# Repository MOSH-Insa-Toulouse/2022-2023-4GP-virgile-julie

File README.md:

# 2022-2023-4GP-virgile-julie
Projet 4GP du capteur au banc de test en open source hardware
---
## Sommaire
  - [1) Livrables](#1-livrables)
  - [2) Description](#2-description)
  - [3) Shield PCB](#3-shield-pcb)
  - [4) Arduino](#4-arduino)
  - [5) Application Android APK](#5-application-android-apk)
  - [6) Banc de test et mesures](#6-banc-de-test-et-mesures)
  - [7) Datasheet](#7-datasheet)
  - [8) Limites et perspectives](#8-Limites-et-perspectives)
---
## 1) Livrables

Lors de notre projecteur, nous avons décidé de réaliser l'ensemble des options (headers) sur la schématique du shield: 
- capteur
- module bluetooth
- flex sensor
- écran OLED
- potentiomètre digital
 
 Pour se faire, nous avons du réaliser un cahier des charges adaptés:
 
-  Réalisation d'un Shield PCB sur KiCad
-  Réalisation d'un code Arduino permettant la mesure du capteur, ainsi que le réglage du potentiomètre, l'affichage sur un écran OLED, l'envoie des données par module Bluetooth
- Réalisation d'une Application android APK réalisée avec MIT APP INVENTOR
- Réalisation d'une Datasheet du capteur
---
## 2) Description

Dans ce projet, nous allons concevoir un capteur résistif fonctionnant sur la base d'un phénomène physique observé qui est l'effet tunnel. En faisant varier la distance séparant les particules du réseau( par des déformations en compression et en tension), on modifie la conductivité du graphite.

Pour appliquer ce phènomène, la jauge de contrainte sera peu couteuse. Elle se présente sous la forme d’un U en papier, sur lequel on vient déposer du graphite à l’aide d’un crayon à papier ceci est très simple à réaliser et sa fabrication ne génère pas d’impact négatif sur l’environnement. A noter aussi que la réponse du capteur va dépendre du type de mine utilisée. 

Nous avons débuté notre projet par la fabrication de notre shield pour notre chaine de mesures. Ce dernier a été conçu a l'aide du logiciel KICAD  sur la base du amplificateur transimpédance simulation électrique du circuit associé au shield sur le logiciel LTSpice.

Pour exploiter le signal de sortie du capteur par un convertisseur analogique-numérique d’une carte Arduino, la sortie du capteur est reliée à un circuit amplificateur transimpédance. Ce circuit dispose de trois étages de filtrage : 
- Un filtre passe-bas R1C1 qui permet de filtrer les bruits en courants sur le signal d’entrée
- Un filtre passe bas R3C4 couplé à un amplificateur opérationnel LTC1050 permettant de filtrer la composante du bruit à 50 Hz provenant du réseau électrique
- Un filtre de sortie R5C2 qui coupe les bruits due à l’échantillonnage de l’ADC
On retrouve la valeur de résistance du capteur grâce à la formule suivante : 
R=(1+R3/R2)*R1*Vcc/Vadc-R1-R5

Par la suite, nous avons ensuite imprimé notre circuit PCB après validation de celle-ci, qui aura demandé de multiples essais. 
Puis, nous avons réalisé le montage des composants sur la carte vierge avec le matériel ci-dessous.

Matériel nécessaire
* 1 carte Arduino Uno
* 2 Résistance de 100kΩ
* 1 Résistance de 1kΩ
* 1 Potentiomètre digital MCP-41050
* 2 Condensateurs 100nF
* 1 Condensateurs 1µF
* 1 AOP LTC1050
* 1 Écran OLED01
* 1 Module Bluetooth HC-05

Puis, nous avons codé avec l'usage d'une carte Arduino le code permettant la lecture des mesures du capteur ainsi que l'ajout sur le code des fonctions associés aux différentes options ajoutés soit l'écran OLED, le module Bluetooth et le potentiomètre digital.  
Ensuite, nous avons développé une application Android qui a pour but de recevoir des données via Bluetooth grâce le site MIT App Inventor.  
Et enfin, nous avons réalisé notre propre banc de test : nous avons effectué un test de rayon de courbure et un test de répétabilité avec deux types de crayons (2B, HB2).  

---
## 3) Shield PCB

### Réalisation de la Schématique de Shield
Cette partie se consacre à la réalisation et la fabrication du support éléctronique, soit le PCB de notre projet. Il a été réalisé sur le logiciel Kicad en se basant sur le template d'un arduino uno.

Pour se faire, nous avons conçu l'ensemble des symboles et empreintes associés aux options choisis précédements. Avec les empreintes, nous les avons connecté avec le reste du circuit existant afin d'obtenir notre shield.

### Réalisation de la Schématique du PCB
En se basant sur notre Shield, nous avons réalisé le routage de notre circuit en prenant soin de limiter les distances entre les composantes et leur pins associés. Cette étape fut très laboriseuse car le fait d'avoir une seule couche pour le PCB, nous obligeait de trouver des stratagèmes d'optimisation de place et de placement. Lorsque cette étape était fini, nous pouvons passer à la pose du plan de masse de notre circuit.

Comme nous pouvons le voir, le résultant possède néanmoins un fil supplémentaire, un fil rouge, qui sera ajouté lors de la fabrication du shield pour respecter le plan de masse. 

### Fabrication du PCB
Le PCB a été fabriqué à partir d'une plaquette d’époxy recouverte d’une fine couche de cuivre. 

Etapes de fabrication:

* Réaliser une insolation aux UVs de notre plaquette avec le calque de notre circuit (10 minutes)
* Retirer la partie de résine non isolée avec un révélateur
* Plonger notre plaquette dans un bain de percholorure de fer

### Assemblage des composantes
Lorsque le PCB a été fabriqué, il nous reste l'étape d'assemblage du shield. Pour se faire, il nous faut donc percer le PCB et souder les composants.
Pour ce qui est du perçage, dans les consignes, il était dit de prévoir deux tailles de trous sur le Kicad, soit un de diamètre 0,8mm pour les composants et headers et un de diamètre 1mm pour les broches de connexion de la carte Arduino Uno.

## 4) Arduino

Nous avons développé un code Arduino qui permet de récupérer la valeur amplifiée de la résistance du capteur de l’afficher sur l’écran OLED et de l’envoyer au module Bluetooth. De plus, il traite la valeur de la résistance du flex sensor et affiche sa valeur de déformation sur l’écran OLED. La communication avec l'écran OLED se fait grâce à la bibliothèque Adafruit_SSD1306.h. 
Ce code permet aussi de régler le potentiomètre digital, qui remplace la valeur de R2 dans le circuit électrique. 

## 5) Application Android APK

Nous avons développé une application android à l’aide du développeur MIT App Inventor. Couplée au module Bluetooth HC-05, cette application permet d’afficher en direct la résistance du capteur et l’évolution de la résistance en fonction du temps grâce à  un graphique déroulant.

Voici le schéma block de notre application : 

Le graphique déroulant permet une analyse qualitative plus que quantitative car le graphique déroulant n’a pas d’échelle en ordonnée. 
Les limites de cette application sont : 
-	Si on lance l’application alors que la carte Arduino tournait déjà, il y a une erreur car l’application ne reçoit pas une seule valeur numérique mais plusieurs
-	Si l’application reçoit la valeur infinie, l’application affiche une erreur 

## 6) Banc de test et mesures 

Un banc de test présentant différents arcs de cercle de différents diamètres a été utilisé pour les mesures de caractéristiques électriques. Le but est de mesurer la variation de résistance entre le capteur « à plat » et le capteur courbé sur les arcs de cercle. 
En désignant r le rayon du cercle et e l’épaisseur du banc de test, on calcule la déformation de chaque arc de cercle à partir de cette formule : ε = e / 2r 

Nous avons testé notre capteur avec deux crayons différents : un avec une mine 2B et un avec une mine HB2.

Caractéristique du capteur en tension en fonction d’un pourcentage de déformation pour un crayon 2B

Caractéristique du capteur en tension en fonction d’un pourcentage de déformation pour un crayon HB2

## 7) Datasheet

Vous trouverez le lien vers la datasheet du capteur : [Datasheet](https://github.com/MOSH-Insa-Toulouse/2022-2023-4GP-virgile-julie/blob/main/Datasheet_capteur/datasheet.pdf)

## 8) Limites et perspectives

La réponse du capteur dépend grandement de la quantité déposée de graphite, ce qui est difficilement mesurable dans le cas du dépot avec une mine de crayon. 

La valeur de la résistance du potentiomète est modifiable seulement au niveau du code : si on veut modifier sa valaeur, il faut modifier le code. On peut imaginer un dispositif qui permet de modifier sa valeur grâce à l'ajout d'un composant au niveau du Hardware, comme par exemple un encodeur rotatif.

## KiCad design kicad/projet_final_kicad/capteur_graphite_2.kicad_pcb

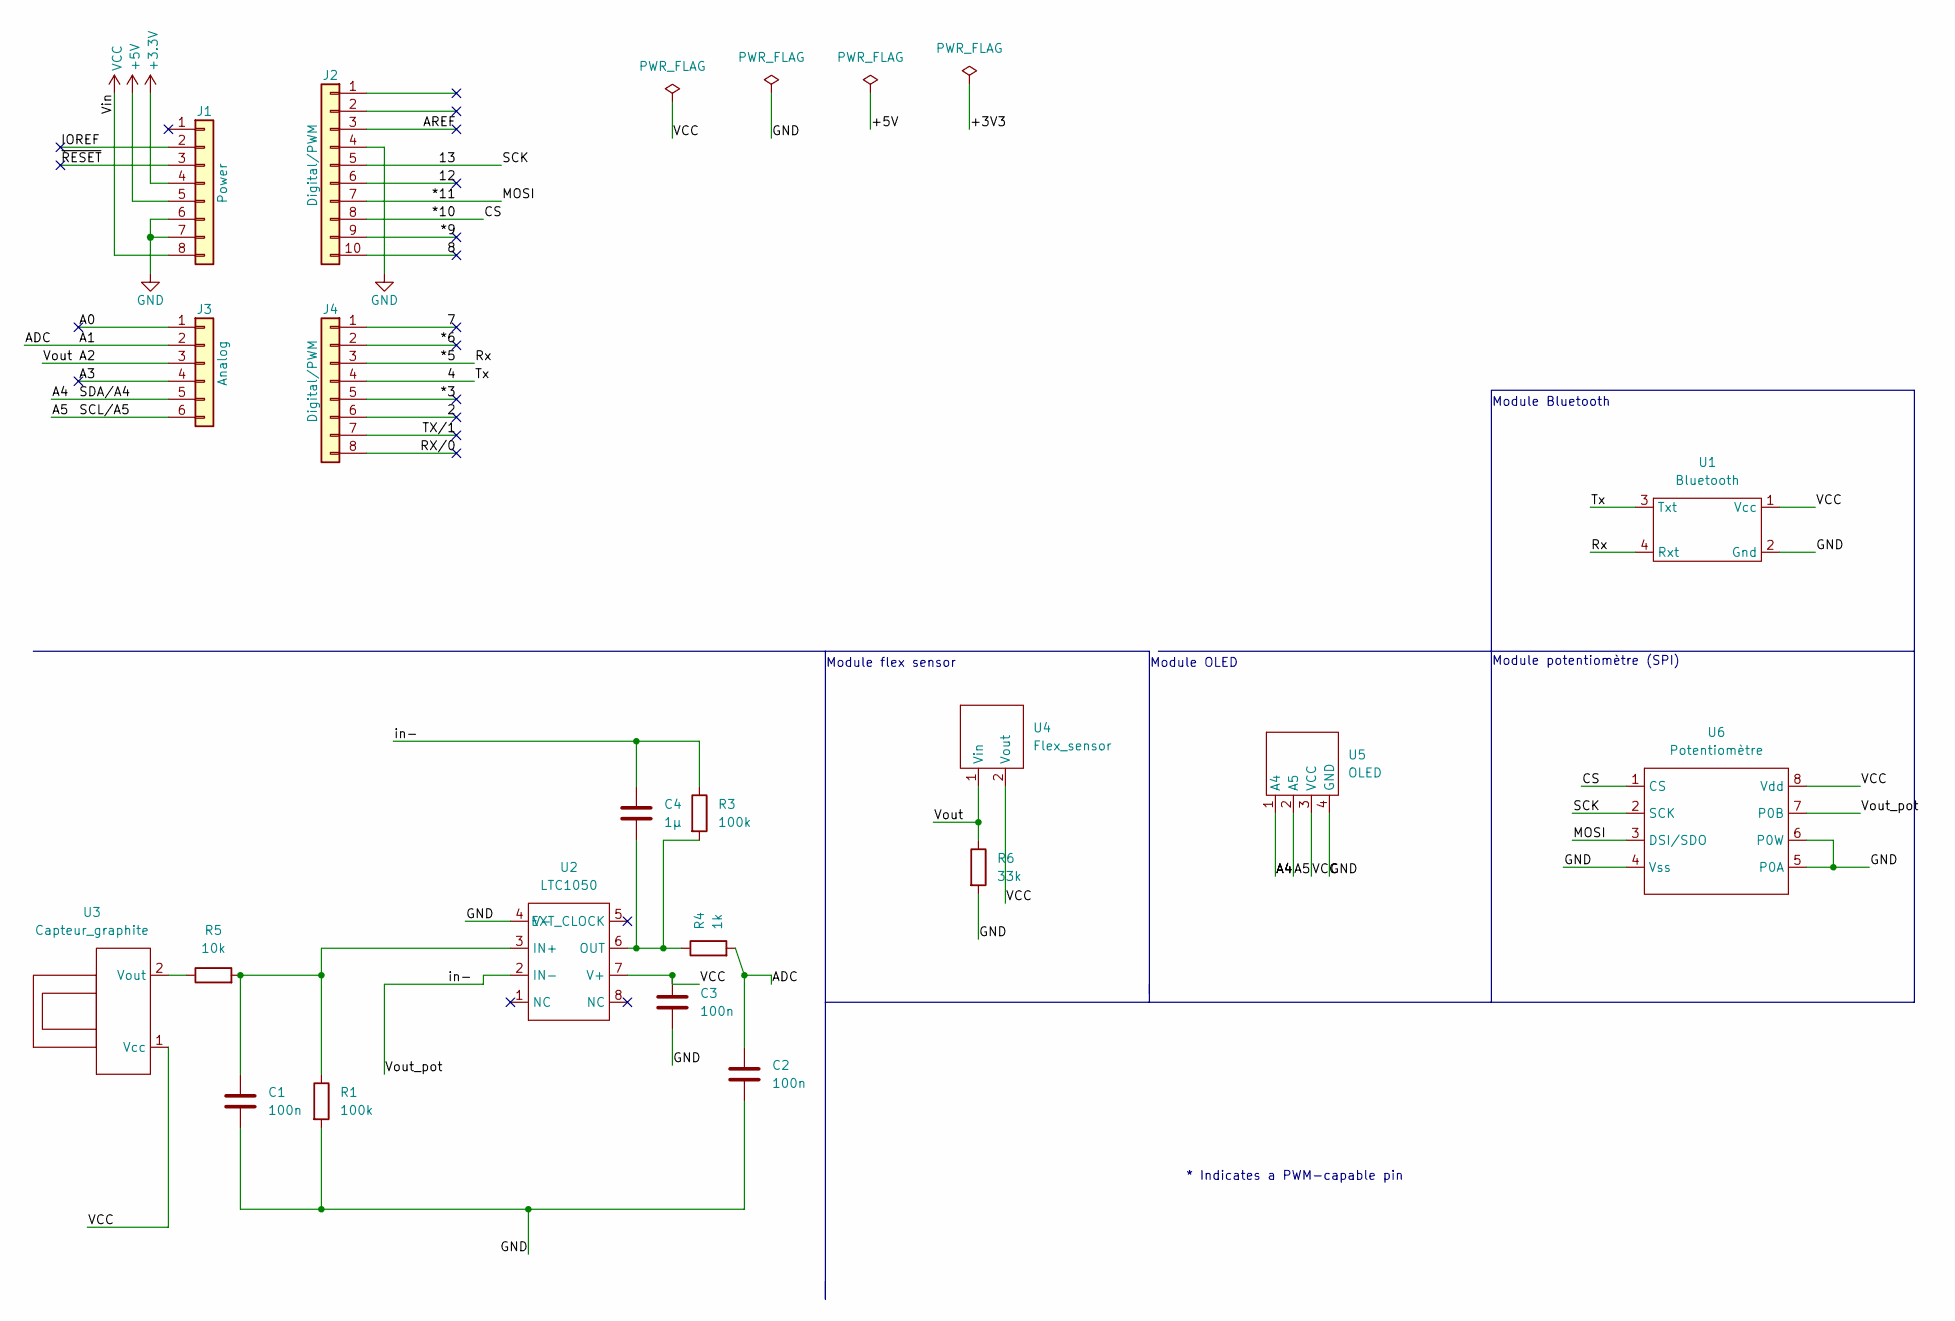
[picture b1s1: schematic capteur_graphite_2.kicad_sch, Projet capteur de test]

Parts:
C1, C2, C3: 100n; C_Axial_L3.8mm_D2.6mm_P7.50mm_Horizontal
C4: 1µ; C_Axial_L3.8mm_D2.6mm_P7.50mm_Horizontal
J1: Power; PinSocket_1x08_P2.54mm_Vertical
J2: Digital/PWM; PinSocket_1x10_P2.54mm_Vertical
J3: Analog; PinSocket_1x06_P2.54mm_Vertical
J4: Digital/PWM; PinSocket_1x08_P2.54mm_Vertical
R1, R3: 100k; R_Axial_DIN0207_L6.3mm_D2.5mm_P10.16mm_Horizontal
R4: 1k; R_Axial_DIN0207_L6.3mm_D2.5mm_P10.16mm_Horizontal
R5: 10k; R_Axial_DIN0207_L6.3mm_D2.5mm_P10.16mm_Horizontal
R6: 33k; R_Axial_DIN0207_L6.3mm_D2.5mm_P10.16mm_Horizontal
U1: Bluetooth
U2: LTC1050; LTC
U3: Capteur_graphite
U4: Flex_sensor; Flex sensor
U5: OLED
U6: Potentiomètre; Pot

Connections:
+3V3: J1.4
+5V: J1.5
/2: J4.6
/4: J4.4, U1.3 (Txt)
/7: J4.1
/8: J2.10
/12: J2.6
/13: J2.5, U6.2 (SCK)
/*3: J4.5
/*5: J4.3, U1.4 (Rxt)
/*6: J4.2
/*9: J2.9
/*10: J2.8, U6.1 (CS)
/*11: J2.7, U6.3 (DSI/SDO)
/A0: J3.1
/A1: C2.2, J3.2, R4.2
/A2: J3.3, R6.1, U4.1 (Vin)
/A3: J3.4
/A4: J3.5, U5.1 (A4)
/A5: J3.6, U5.2 (A5)
/AREF: J2.3
/IOREF: J1.2
/RX/0: J4.8
/TX/1: J4.7
/Vout_pot: C4.1, R3.1, U2.2 (IN-), U6.7 (P0B)
/~RESET: J1.3
GND: C1.2, C2.1, C3.2, J1.6, J1.7, J2.4, R1.2, R6.2, U1.2 (Gnd), U2.4 (NC), U5.4 (GND), U6.4 (Vss), U6.5 (P0A), U6.6 (P0W)
unnamed: C1.1, R1.1, R5.2, U2.3 (IN+)
unnamed: C4.2, R3.2, R4.1, U2.6 (V+)
unnamed: R5.1, U3.2 (Vout)
VCC: C3.1, J1.8, U1.1 (Vcc), U2.7 (OUT), U3.1 (Vcc), U4.2 (Vout), U5.3 (VCC), U6.8 (Vdd)

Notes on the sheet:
Module OLED
Module flex sensor
Module potentiomètre (SPI)
Module Bluetooth
* Indicates a PWM-capable pin

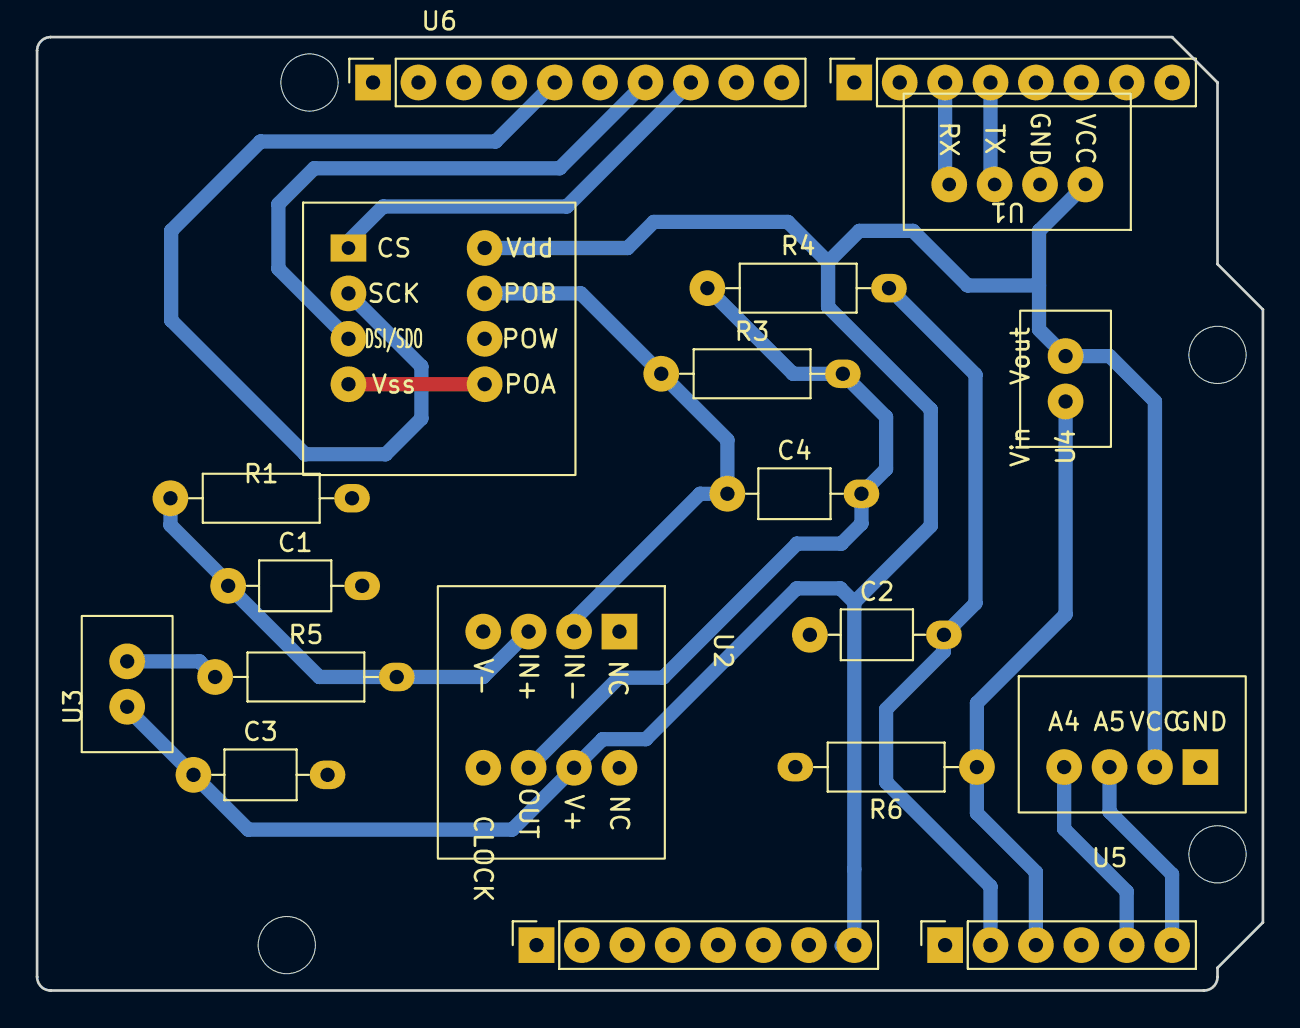
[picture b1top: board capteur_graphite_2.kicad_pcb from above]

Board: 2 copper layers, 68.6 x 53.3 mm, 23 parts (0 on the bottom side), 15 nets.

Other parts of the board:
MH1, MH2, MH3, MH4: MountingHole_3.2mm

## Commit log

2023-02-01 Ajout TODO list
2023-02-01 hola
2023-02-01 rassemblement
2023-05-15 Create Kicad
2023-05-15 ajouter datasheet docx
2023-05-15 dossier final
2023-05-30 Revert "Update README.md"
